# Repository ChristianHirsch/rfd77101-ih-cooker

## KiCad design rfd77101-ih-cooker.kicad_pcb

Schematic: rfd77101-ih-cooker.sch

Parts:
C1: 10n; C_0603_1608Metric
C2: 100n; C_0603_1608Metric
C3, C4, C5, C6: 1u; C_0603_1608Metric
D3: LED; LED_0603_1608Metric
J1: Conn_01x02; TerminalBlock_RND_205-00067_1x02_P7.50mm_Horizontal
J2: Conn_input; PinHeader_1x10_P2.54mm_Vertical
J3: Conn_01x07; PinHeader_1x07_P2.54mm_Vertical
J4: Conn_output; PinHeader_1x10_P2.54mm_Vertical
Q1, Q2: BSS138; SOT-23
R1, R2, R3, R5, R6: 10k; R_0603_1608Metric
R4: 100; R_0603_1608Metric
R7: 6.8k; R_0603_1608Metric
R8: 1k; R_0603_1608Metric
R9: 1.5k; R_0603_1608Metric
R10: 100k; R_0603_1608Metric
U1: RFD77101; RFDigital_RFD77101
U2: MAX31855KASA; SOIC-8_3.9x4.9mm_P1.27mm
U3: AP2204K-3.0; SOT-23-5
U4: MCP6002-xMC; DFN-8-1EP_3x2mm_P0.5mm_EP1.75x1.45mm

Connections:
+5V: C3.1, J2.4, J4.4, R2.1, R5.1, U3.1 (VIN), U3.3 (EN), U4.8
/1: J2.1, J4.1
/2: J2.2, J4.2
/5: J2.5, J4.5
/6: J2.6, J4.6
/7: J2.7, J4.7
/10: J2.10, J4.10
/GPIO0: J3.6, U1.25
/GPIO1: J3.7, U1.23
/IO_I: J2.8, Q2.3, R5.2
/IO_O: J4.8, Q1.3, R2.2
/LED_1: D3.2, U1.11
/LV_I: Q2.2, R3.2, U1.17
/LV_O: Q1.2, R1.2, U1.18
/LV_Power_I: R8.2, R9.1, U1.22
/LV_Power_O: C6.1, R10.1, U4.3
/MISO: U1.27, U2.7
/Power_I: J2.9, U4.5
/Power_O: J4.9, R7.1, U4.1
/SCK: U1.29, U2.5
/SWDCLK: J3.5, U1.9
/SWDIO/RESET: J3.4, U1.8
/~SS: U1.28, U2.6
GND: C2.2, C3.2, C4.2, C5.2, C6.2, J2.3, J3.1, J4.3, R4.2, R6.2, R9.2, U1.1, U1.2, U1.4, U1.6, U1.19, U1.30, U1.42, U1.43, U1.44, U1.45, U2.1, U3.2 (GND), U4.4, U4.9
unnamed: C1.1, J1.2, U2.3
unnamed: C1.2, J1.1, U2.2
unnamed: D3.1, R4.1
unnamed: R6.1, R7.2, U4.2
unnamed: R8.1, U4.6, U4.7
unnamed: R10.2, U1.14
VDD: C2.1, C4.1, C5.1, J3.3, Q1.1, Q2.1, R1.1, R3.1, U1.7, U2.4, U3.5 (VOUT)

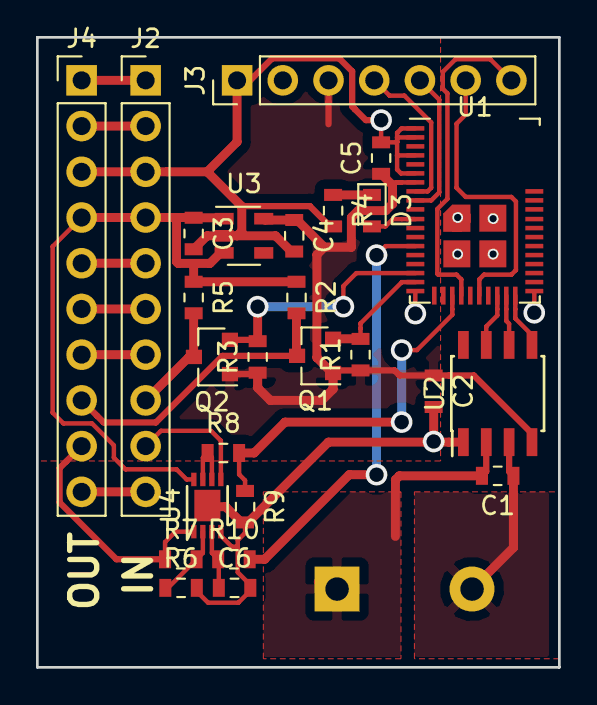
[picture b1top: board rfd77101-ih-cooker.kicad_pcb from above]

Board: 2 copper layers, 29.0 x 35.0 mm, 27 parts (1 on the bottom side), 31 nets.

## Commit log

2018-07-19 minors
